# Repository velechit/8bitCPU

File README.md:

Inspired by Ben Eater's 8-bit breadboard computer, but with several improvements

Refer to module wise README.md for corresponding changes and deviation from Ben Eater's design.

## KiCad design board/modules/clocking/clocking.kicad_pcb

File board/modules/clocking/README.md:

Clock module schematic is ready for reviews and feedbacks. improvements in clock module: 
1. Astable clock is 50% duty cycle 
2. when clock source changes inbetween a high pulse, clock glitches. this has been eliminated by synchronising the clock source selection to the clocks using additional NE555
3. Halt signal keeps the Astable NE555 reset unlike gated at output in Ben Eater's design, Maybe a very small power saving?

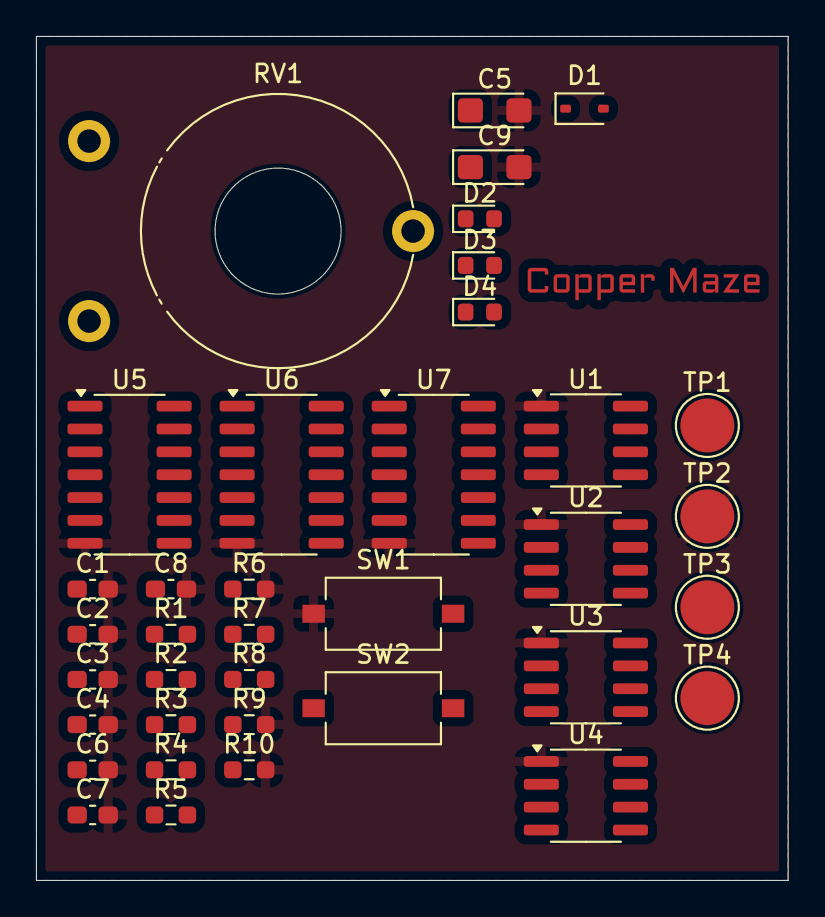
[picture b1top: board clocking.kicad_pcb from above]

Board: 2 copper layers, 41.8 x 46.9 mm, 37 parts (0 on the bottom side), 34 nets, no tracks yet.

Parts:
C1: 1u; C_0603_1608Metric_Pad1.08x0.95mm_HandSolder
C2, C3, C4, C6, C7, C8: 100n; C_0603_1608Metric_Pad1.08x0.95mm_HandSolder
C5: 10u; CP_EIA-3216-18_Kemet-A
C9: 100u; CP_EIA-3216-18_Kemet-A
D1: 1N4148; D_SOD-323
D2: GREEN; LED_0603_1608Metric
D3: RED; LED_0603_1608Metric
D4: WHITE; LED_0603_1608Metric
R1, R2, R3, R4, R8, R9, R10: 1k; R_0603_1608Metric_Pad0.98x0.95mm_HandSolder
R5, R6: 10k; R_0603_1608Metric_Pad0.98x0.95mm_HandSolder
R7: 100k; R_0603_1608Metric_Pad0.98x0.95mm_HandSolder
RV1: 1Meg; Potentiometer_Piher_PT-15-V15_Vertical_Hole
SW1: CLK; SW_Tactile_SPST_NO_Straight_CK_PTS636Sx25SMTRLFS
SW2: SEL; SW_Tactile_SPST_NO_Straight_CK_PTS636Sx25SMTRLFS
TP1: VCC; TestPoint_Pad_D3.0mm
TP2: GND; TestPoint_Pad_D3.0mm
TP3: HALT; TestPoint_Pad_D3.0mm
TP4: Output; TestPoint_Pad_D3.0mm
U1, U2, U3, U4: NE555D; SOIC-8_3.9x4.9mm_P1.27mm
U5: 7404; SOIC-14_3.9x8.7mm_P1.27mm
U6, U7: 7400; SOIC-14_3.9x8.7mm_P1.27mm

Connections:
+5V: C8.1, C9.1, D3.2 (A), R1.1, R3.1, R4.1, R5.1, TP1.1, U1.8 (VCC), U2.8 (VCC), U3.4 (R), U3.8 (VCC), U4.8 (VCC), U5.14 (VCC), U6.14 (VCC), U7.14 (VCC)
/FRC: U1.3 (Q), U5.1, U6.1
/FRC_rst_sync: U6.3, U7.1, U7.9
/HALT: TP3.1, U6.5, U7.2
/MCC: U2.3 (Q), U5.3, U7.5
/MCC_rst_sync: U6.4, U7.6, U7.10
GND: C1.2, C2.2, C3.2, C4.2, C5.2, C6.2, C7.2, C8.2, C9.2, R6.2, R9.2, R10.2, SW1.1, TP2.1, U1.1 (GND), U2.1 (GND), U3.1 (GND), U4.1 (GND), U5.7 (GND), U6.7 (GND), U7.7 (GND)
unnamed: C1.1, RV1.2, RV1.3
unnamed: C5.1, R7.2, SW2.1
unnamed: D1.2 (A), R1.2, R2.1, U1.7 (DIS)
unnamed: D1.1 (K), R2.2, RV1.1, U1.2 (TR), U1.6 (THR)
unnamed: D2.2 (A), R8.2, U4.3 (Q), U5.11, U6.2
unnamed: D2.1 (K), R9.1
unnamed: D3.1 (K), R8.1
unnamed: D4.2 (A), TP4.1, U7.8
unnamed: D4.1 (K), R10.1
unnamed: C2.1, U1.5 (CV)
unnamed: U1.4 (R), U7.3
unnamed: C4.1, U2.5 (CV)
unnamed: C3.1, R4.2, U2.6 (THR), U2.7 (DIS)
unnamed: U2.4 (R), U6.6
unnamed: R3.2, SW1.2, U2.2 (TR)
unnamed: C6.1, U3.5 (CV)
unnamed: R7.1, U3.3 (Q), U5.9, U6.12
unnamed: R5.2, R6.1, SW2.2, U3.2 (TR), U3.6 (THR)
unnamed: C7.1, U4.5 (CV)
unnamed: U4.4 (R), U6.8
unnamed: U4.2 (TR), U6.11
unnamed: U5.2, U7.12
unnamed: U5.4, U7.13
unnamed: U5.5, U7.11
unnamed: U5.6, U6.10, U6.13
unnamed: U5.8, U6.9
unnamed: U5.10, U7.4

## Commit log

2025-03-20 Adding README.md
2025-03-20 Updating README
2025-03-20 Updating Library
2025-03-20 1. Update to Local Symbol Library 2. Clocking Module Schematic
2025-03-20 Updating Schematic PDF
2025-03-20 README.md
2025-03-20 Spell Check
2025-03-20 Updating README.md
2025-03-21 Updating Footprint Mapping
2025-03-21 Updating Schemtic
2025-03-21 Updating Schematic
2025-03-21 Latest Schematic as PDF
2025-03-25 Correction in Astable
2025-03-25 New PDF Dump of schematic
